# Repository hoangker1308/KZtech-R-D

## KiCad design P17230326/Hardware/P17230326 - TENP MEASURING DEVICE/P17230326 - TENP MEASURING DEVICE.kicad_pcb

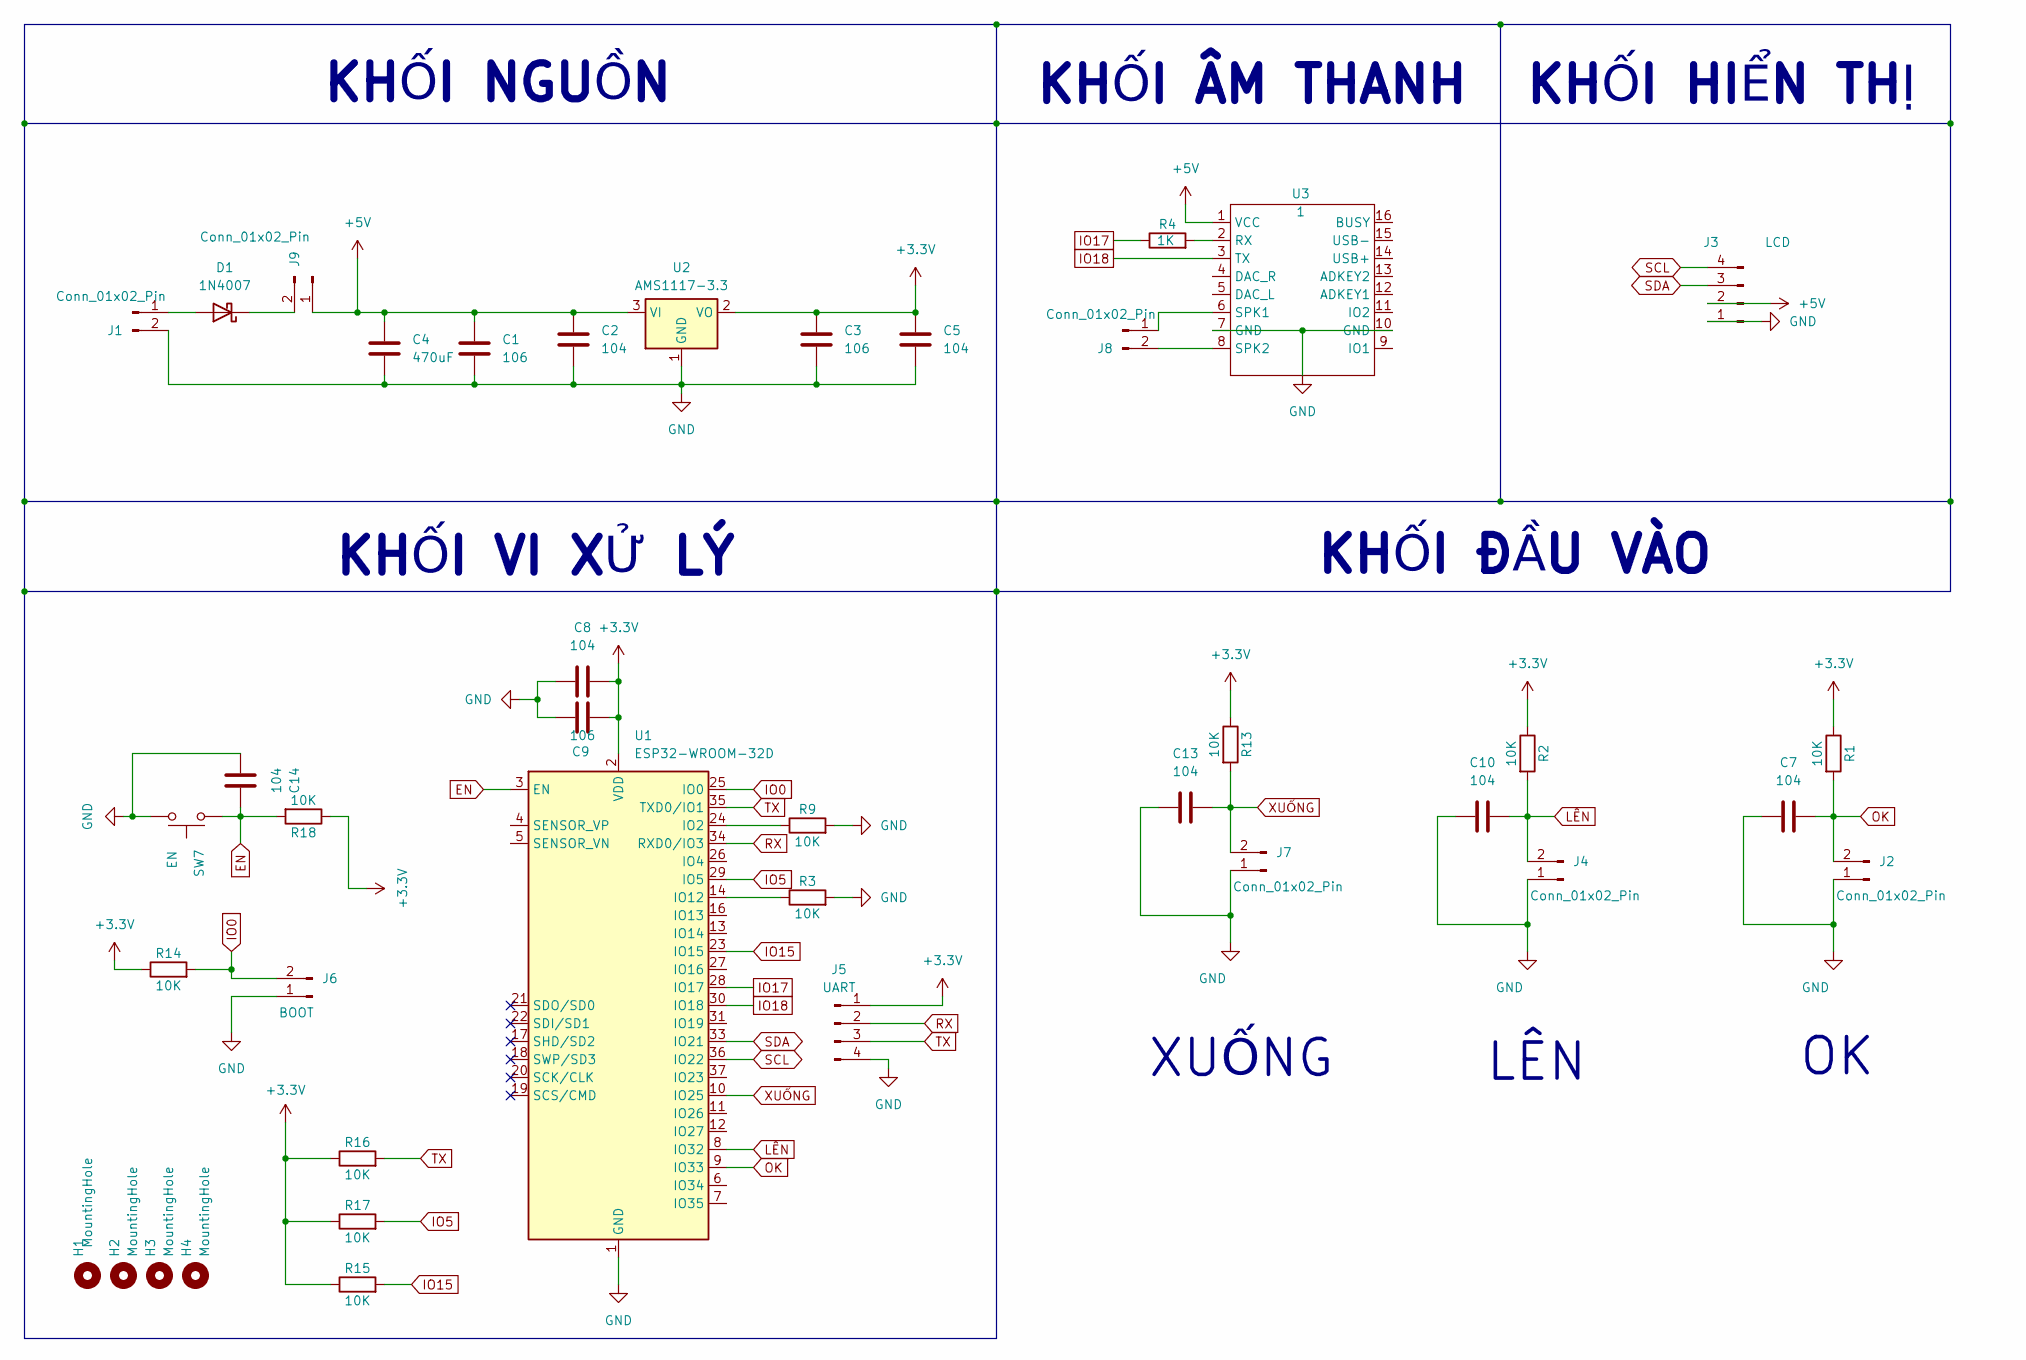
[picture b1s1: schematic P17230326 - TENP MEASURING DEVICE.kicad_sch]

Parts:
C1, C3, C9: 106; C_0805_2012Metric
C2, C5, C7, C8, C10, C13, C14: 104; C_0603_1608Metric
C4: 470uF; C_Radial_D6.3mm_H5.0mm_P2.50mm
D1: 1N4007; D_MELF
H1, H2, H3, H4: MountingHole; MountingHole_3.2mm_M3
J1, J2, J4, J7, J8, J9: Conn_01x02_Pin; JST_XH_B2B-XH-A_1x02_P2.50mm_Vertical
J3: LCD; FanPinHeader_1x04_P2.54mm_Vertical
J5: UART; PinHeader_1x04_P2.54mm_Vertical
J6: BOOT; PinHeader_1x02_P2.54mm_Vertical
R1, R2, R3, R9, R13, R14, R15, R16, R17, R18: 10K; R_0603_1608Metric
R4: 1K; R_0603_1608Metric
SW7: EN; SW_SPST_CK_RS282G05A3
U1: ESP32-WROOM-32D
U2: AMS1117-3.3; SOT-223-3_TabPin2
U3: 1; DFPlayer Mini

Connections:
+3.3V: C3.1, C5.1, C8.2, C9.2, J5.1, R1.1, R2.1, R13.1, R14.1, R15.1, R16.1, R17.1, R18.1, U1.2 (VDD), U2.2 (VO)
+5V: C1.1, C2.1, C4.1, J3.2, J9.1, U2.3 (VI), U3.1 (VCC)
EN: C14.2, R18.2, SW7.1, U1.3 (EN)
GND: C1.2, C2.2, C3.2, C4.2, C5.2, C7.1, C8.1, C9.1, C10.1, C13.1, C14.1, J1.2, J2.1, J3.1, J4.1, J5.4, J6.1, J7.1, R3.2, R9.2, SW7.2, U1.1 (GND), U1.15 (GND), U1.38 (GND), U1.39 (GND), U2.1 (GND), U3.7 (GND), U3.10 (GND)
IO0: J6.2, R14.2, U1.25 (IO0)
IO5: R17.2, U1.29 (IO5)
IO15: R15.2, U1.23 (IO15)
IO17: R4.1, U1.28 (IO17)
IO18: U1.30 (IO18), U3.3 (TX)
LÊN: C10.2, J4.2, R2.2, U1.8 (IO32)
unnamed: D1.2 (A), J1.1
unnamed: D1.1 (K), J9.2
unnamed: J8.1, U3.6 (SPK1)
unnamed: J8.2, U3.8 (SPK2)
unnamed: R9.1, U1.24 (IO2)
unnamed: R3.1, U1.14 (IO12)
unnamed: R4.2, U3.2 (RX)
OK: C7.2, J2.2, R1.2, U1.9 (IO33)
RX: J5.2, U1.34 (RXD0/IO3)
SCL: J3.4, U1.36 (IO22)
SDA: J3.3, U1.33 (IO21)
TX: J5.3, R16.2, U1.35 (TXD0/IO1)
XUỐNG: C13.2, J7.2, R13.2, U1.10 (IO25)

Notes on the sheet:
KHỐI HIỂN THỊ
KHỐI VI XỬ LÝ
XUỐNG
KHỐI ĐẦU VÀO
LÊN
KHỐI NGUỒN
KHỐI ÂM THANH

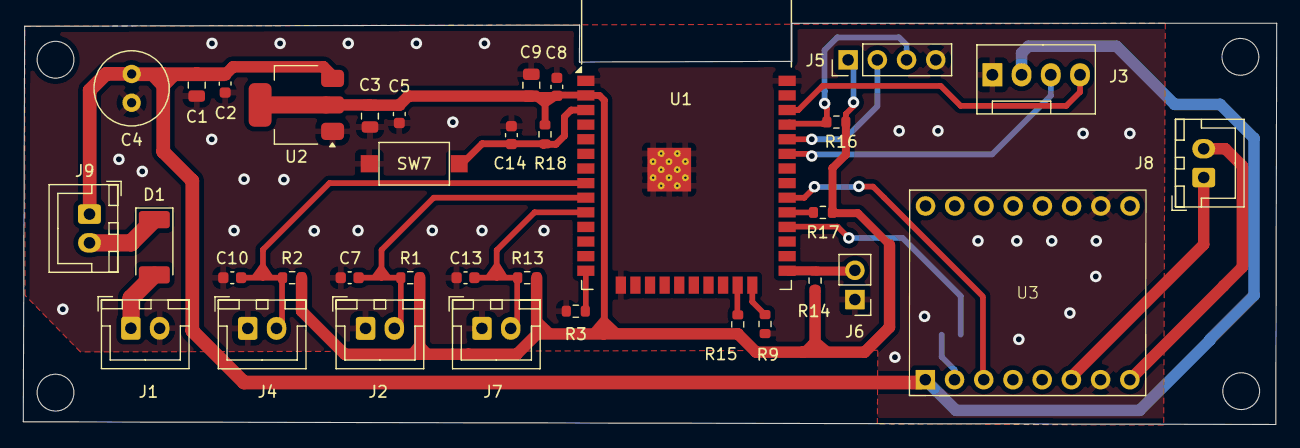
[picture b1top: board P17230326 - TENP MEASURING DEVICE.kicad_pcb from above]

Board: 2 copper layers, 109.0 x 34.9 mm, 40 parts (1 on the bottom side), 23 nets.

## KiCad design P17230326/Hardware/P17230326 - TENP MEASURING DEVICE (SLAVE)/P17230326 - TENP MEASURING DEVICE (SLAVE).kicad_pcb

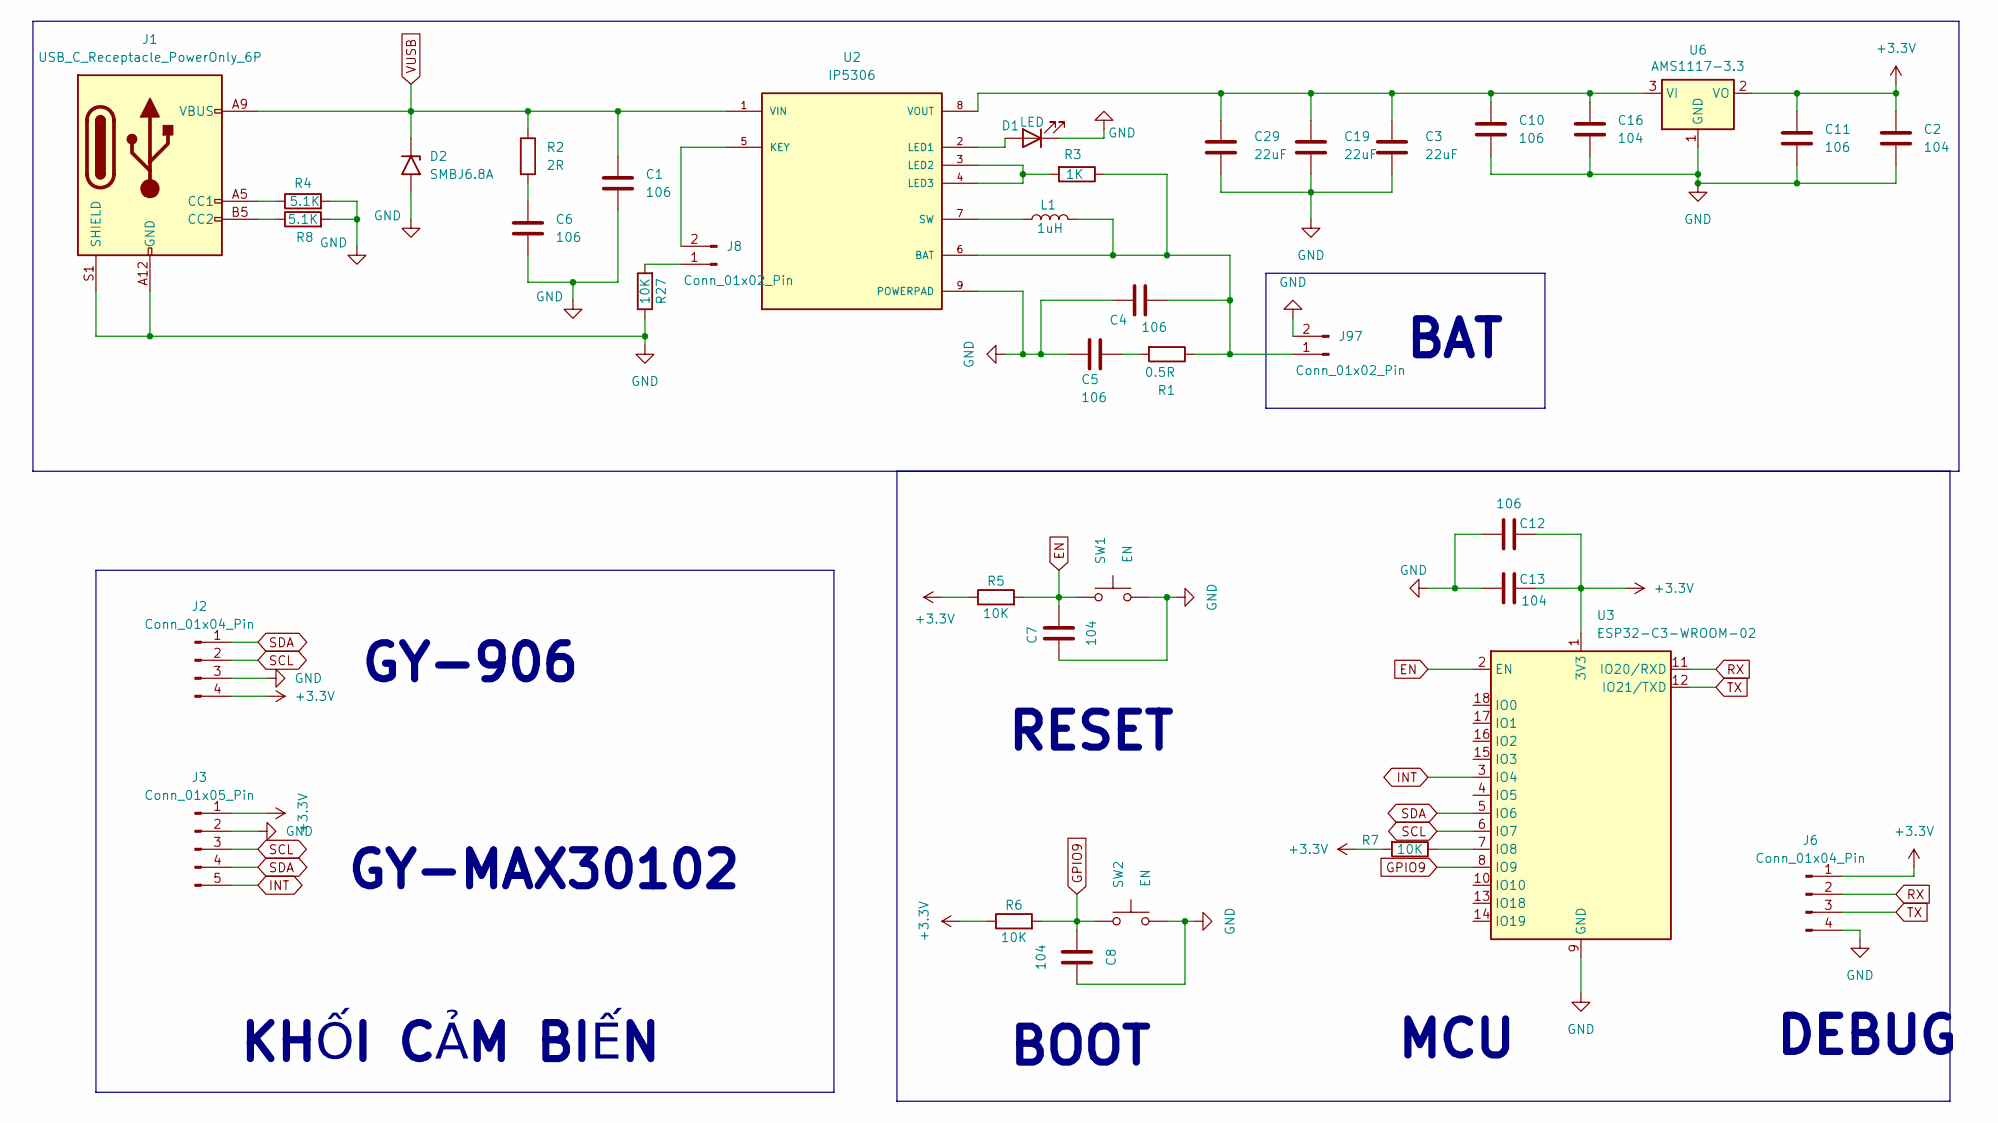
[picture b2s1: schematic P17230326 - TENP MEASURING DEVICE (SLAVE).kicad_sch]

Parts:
C1, C4, C5, C6, C12: 106; C_0805_2012Metric_Pad1.18x1.45mm_HandSolder
C2, C7, C8, C16: 104; C_0603_1608Metric
C3, C19, C29: 22uF; C_0805_2012Metric_Pad1.18x1.45mm_HandSolder
C10, C11: 106; C_0805_2012Metric
C13: 104; C_0603_1608Metric_Pad1.08x0.95mm_HandSolder
D1: LED; LED_D3.0mm
D2: SMBJ6.8A; D_SMB
J1: USB_C_Receptacle_PowerOnly_6P; USB_C_Receptacle_HRO_TYPE-C-31-M-17
J2, J6: Conn_01x04_Pin; PinHeader_1x04_P2.54mm_Vertical
J3: Conn_01x05_Pin; PinHeader_1x05_P2.54mm_Vertical
J8, J97: Conn_01x02_Pin; JST_XH_B2B-XH-A_1x02_P2.50mm_Vertical
L1: 1uH; L_7.3x7.3_H4.5
R1: 0.5R; R_0805_2012Metric_Pad1.20x1.40mm_HandSolder
R2: 2R; R_0805_2012Metric_Pad1.20x1.40mm_HandSolder
R3: 1K; R_0603_1608Metric
R4, R8: 5.1K; R_0603_1608Metric
R5, R6, R27: 10K; R_0603_1608Metric
R7: 10K; R_0603_1608Metric_Pad0.98x0.95mm_HandSolder
SW1, SW2: EN; SW_SPST_CK_RS282G05A3
U2: IP5306; SOIC-8-1EP_3.9x4.9mm_P1.27mm_EP2.41x3.3mm_ThermalVias; PARTREV 1.31
U3: ESP32-C3-WROOM-02
U6: AMS1117-3.3; SOT-223-3_TabPin2

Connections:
+3.3V: C2.1, C11.1, C12.2, C13.2, J2.4, J3.1, J6.1, R5.1, R6.1, R7.2, U3.1 (3V3), U6.2 (VO)
EN: C7.2, R5.2, SW1.1, U3.2 (EN)
GND: C1.2, C2.2, C3.2, C4.1, C5.2, C6.2, C7.1, C8.1, C10.2, C11.2, C12.1, C13.1, C16.2, C19.2, C29.2, D1.1 (K), D2.2 (A2), J1.A12 (GND), J1.B12 (GND), J1.S1 (SHIELD), J2.3, J3.2, J6.4, J97.2, R4.2, R8.2, R27.1, SW1.2, SW2.2, U2.9 (POWERPAD), U3.9 (GND), U3.19 (GND), U6.1 (GND)
GPIO9: C8.2, R6.2, SW2.1, U3.8 (IO9)
INT: J3.5, U3.3 (IO4)
unnamed: C5.1, R1.2
unnamed: C6.1, R2.2
unnamed: D1.2 (A), U2.2 (LED1)
unnamed: J1.A5 (CC1), R4.1
unnamed: J1.B5 (CC2), R8.1
unnamed: J8.1, R27.2
unnamed: J8.2, U2.5 (KEY)
unnamed: C4.2, J97.1, L1.2, R1.1, R3.1, U2.6 (BAT)
unnamed: R3.2, U2.3 (LED2), U2.4 (LED3)
unnamed: L1.1, U2.7 (SW)
unnamed: C3.1, C10.1, C16.1, C19.1, C29.1, U2.8 (VOUT), U6.3 (VI)
unnamed: R7.1, U3.7 (IO8)
RX: J6.2, U3.11 (IO20/RXD)
SCL: J2.2, J3.3, U3.6 (IO7)
SDA: J2.1, J3.4, U3.5 (IO6)
TX: J6.3, U3.12 (IO21/TXD)
VUSB: C1.1, D2.1 (A1), J1.A9 (VBUS), J1.B9 (VBUS), R2.1, U2.1 (VIN)

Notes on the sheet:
GY-906
MCU
KHỐI CẢM BIẾN
GY-MAX30102
DEBUG
RESET
BOOT
BAT

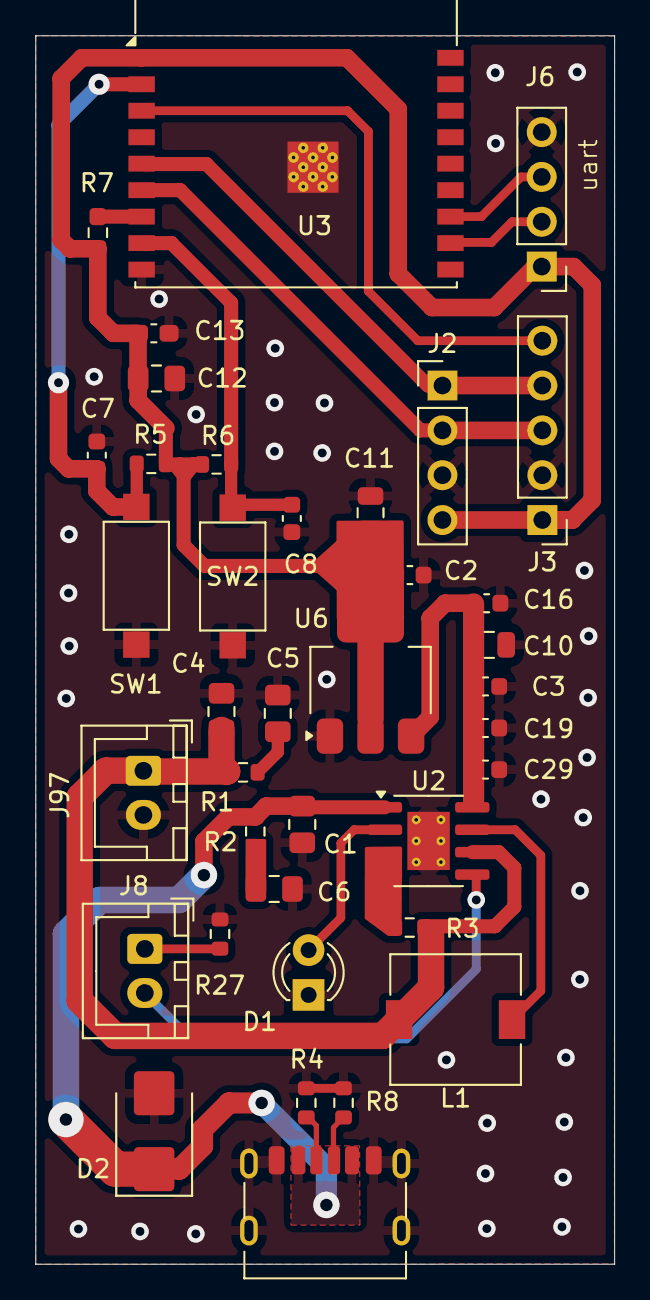
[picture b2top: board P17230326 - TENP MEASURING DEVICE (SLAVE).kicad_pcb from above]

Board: 2 copper layers, 32.8 x 69.6 mm, 38 parts (0 on the bottom side), 22 nets.

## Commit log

2026-05-06 upload folder du an
2026-05-06 P24060526
2026-05-06 text
2026-05-06 ghi chú: cách thêm file mới
